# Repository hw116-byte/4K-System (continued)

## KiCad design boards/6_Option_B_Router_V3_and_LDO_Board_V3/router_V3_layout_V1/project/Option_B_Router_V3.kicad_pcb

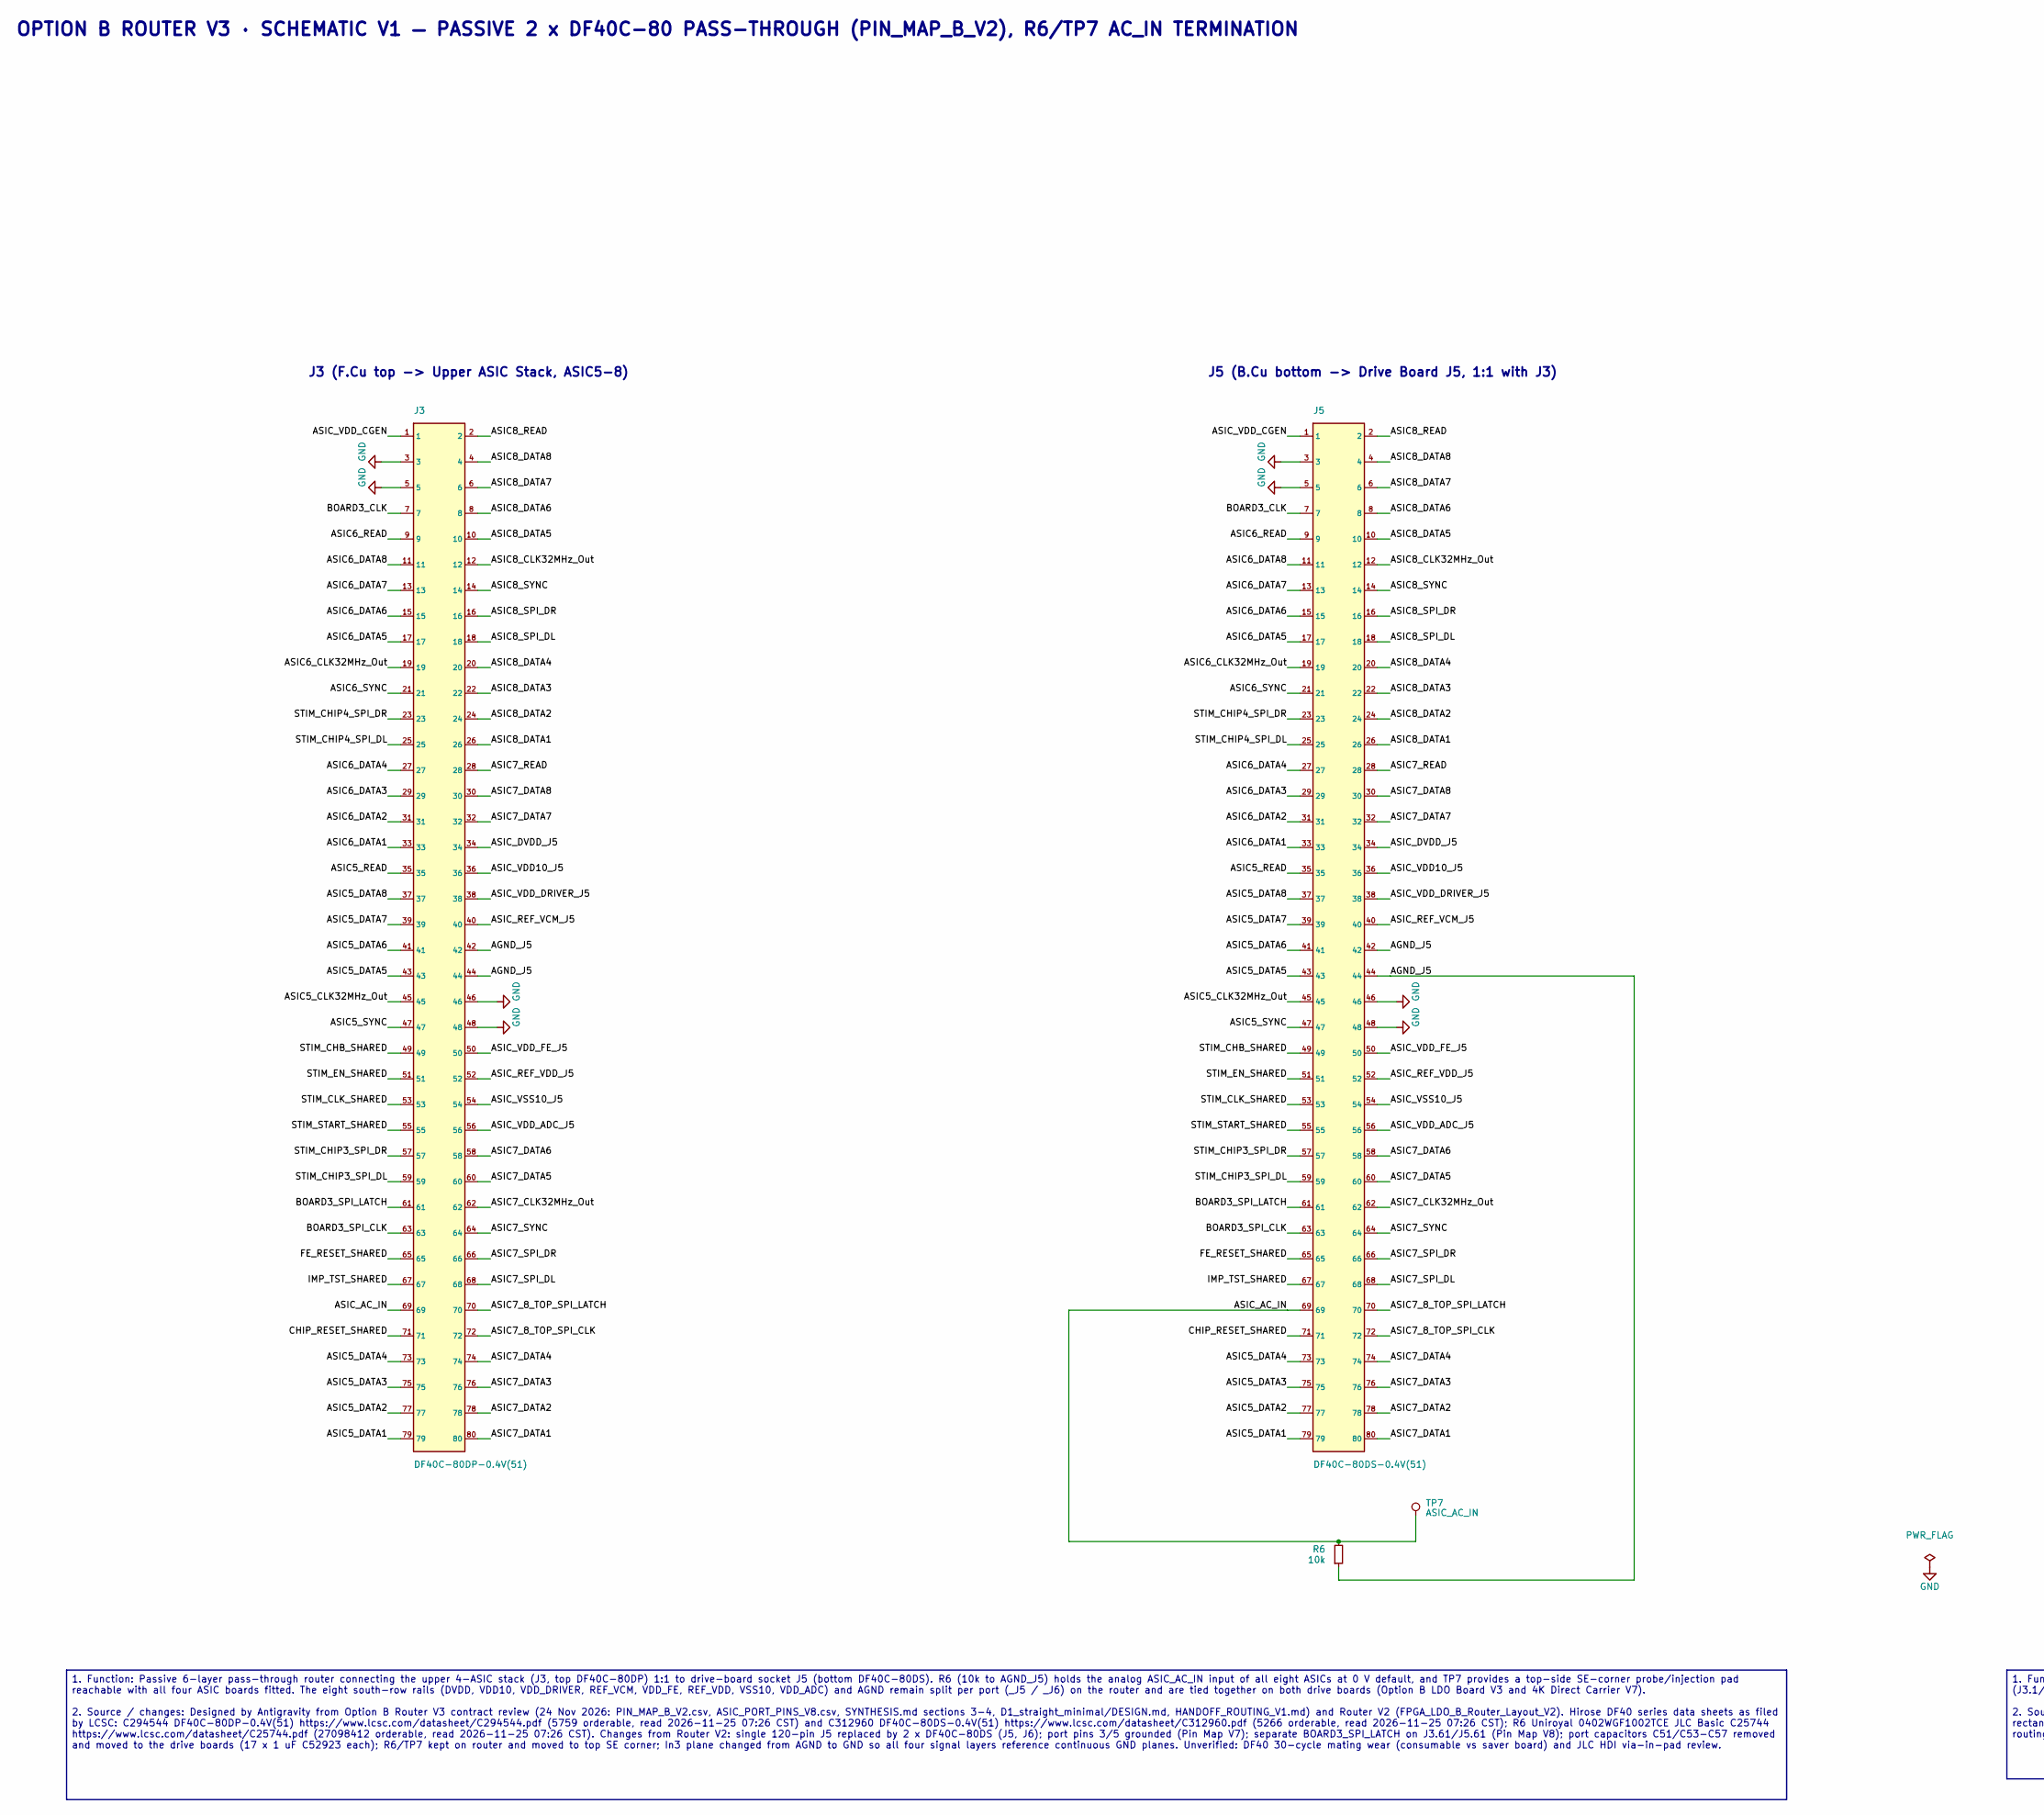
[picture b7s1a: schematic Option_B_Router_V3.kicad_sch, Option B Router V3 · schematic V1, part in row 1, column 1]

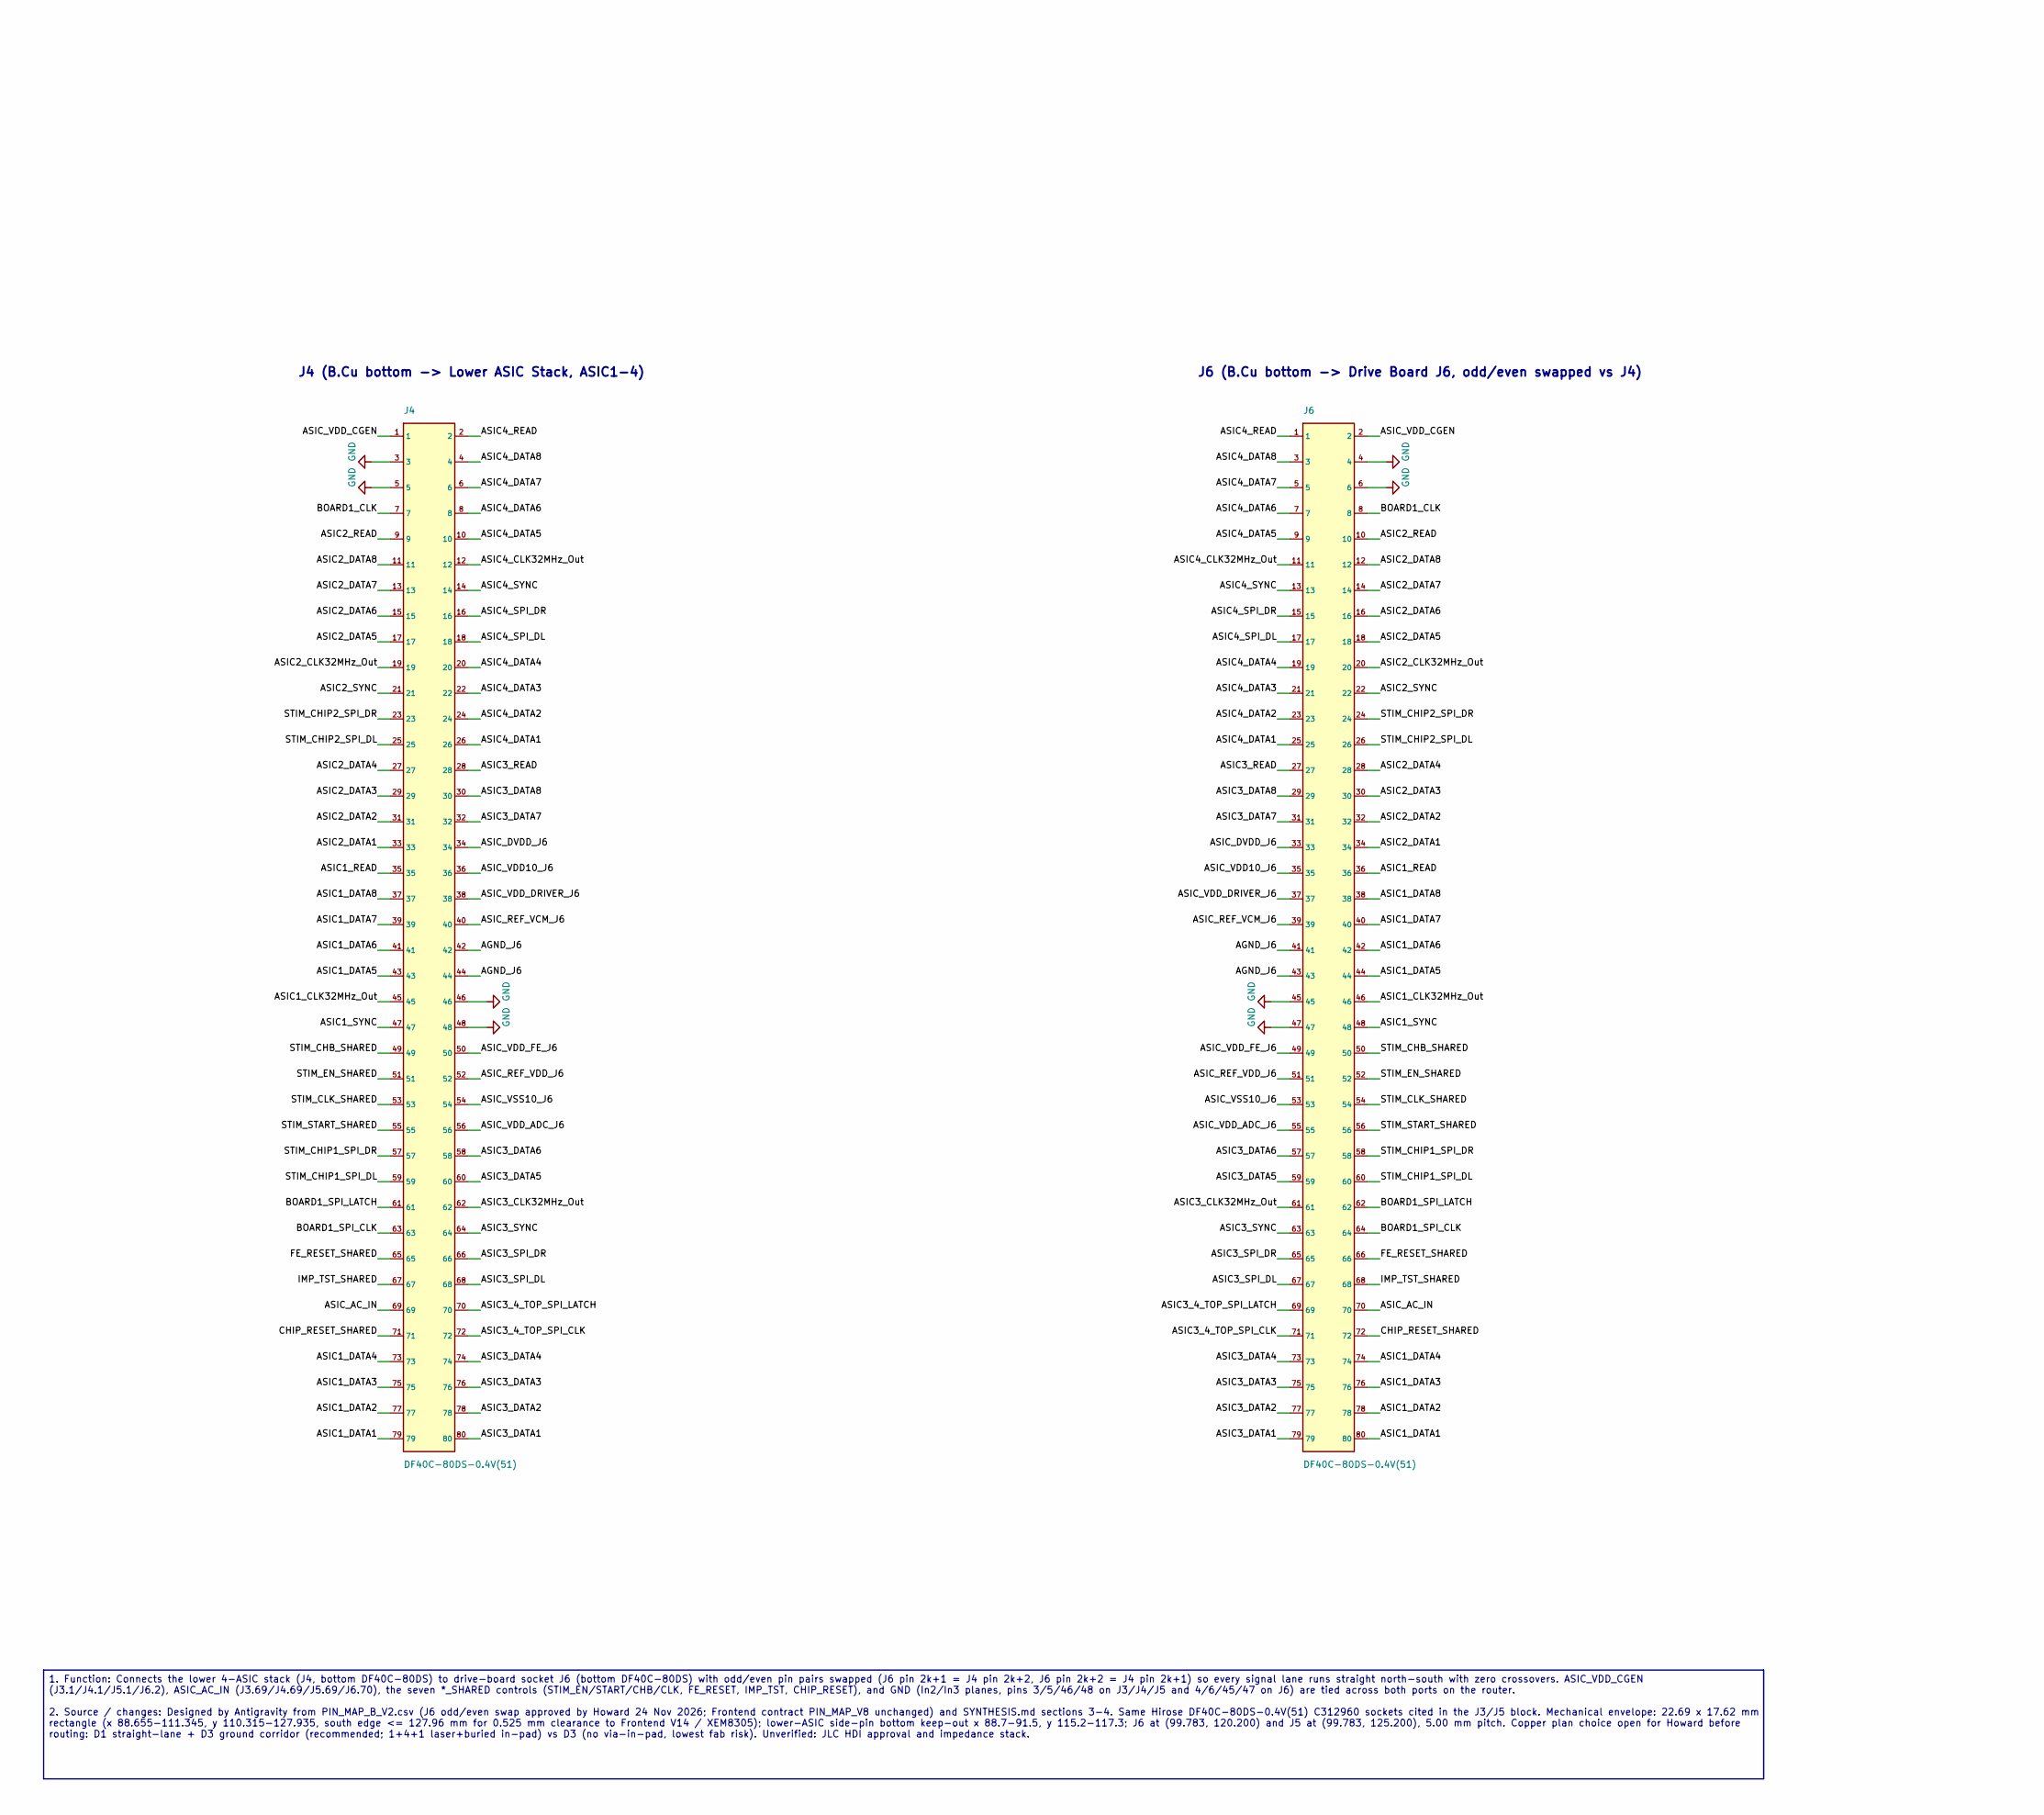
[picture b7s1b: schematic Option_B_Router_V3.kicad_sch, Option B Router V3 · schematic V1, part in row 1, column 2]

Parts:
J3: DF40C-80DP-0.4V(51); Hirose_DF40C-80DP-0.4V_2x40-1MP_P0.4mm; MPN DF40C-80DP-0.4V(51); LCSC C294544
J4, J5, J6: DF40C-80DS-0.4V(51); Hirose_DF40C-80DS-0.4V_2x40_P0.4mm; MPN DF40C-80DS-0.4V(51); LCSC C312960
R6: 10k; R_0402_1005Metric; MPN Uniroyal 0402WGF1002TCE (10k 1% 0402); LCSC C25744
TP7: ASIC_AC_IN; TestPoint_Pad_D1.0mm_Compact

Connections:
/AGND_J5: J3.42, J3.44, J5.42, J5.44, R6.2
/AGND_J6: J4.42, J4.44, J6.41, J6.43
/ASIC1_CLK32MHz_Out: J4.45, J6.46
/ASIC1_DATA1: J4.79, J6.80
/ASIC1_DATA2: J4.77, J6.78
/ASIC1_DATA3: J4.75, J6.76
/ASIC1_DATA4: J4.73, J6.74
/ASIC1_DATA5: J4.43, J6.44
/ASIC1_DATA6: J4.41, J6.42
/ASIC1_DATA7: J4.39, J6.40
/ASIC1_DATA8: J4.37, J6.38
/ASIC1_READ: J4.35, J6.36
/ASIC1_SYNC: J4.47, J6.48
/ASIC2_CLK32MHz_Out: J4.19, J6.20
/ASIC2_DATA1: J4.33, J6.34
/ASIC2_DATA2: J4.31, J6.32
/ASIC2_DATA3: J4.29, J6.30
/ASIC2_DATA4: J4.27, J6.28
/ASIC2_DATA5: J4.17, J6.18
/ASIC2_DATA6: J4.15, J6.16
/ASIC2_DATA7: J4.13, J6.14
/ASIC2_DATA8: J4.11, J6.12
/ASIC2_READ: J4.9, J6.10
/ASIC2_SYNC: J4.21, J6.22
/ASIC3_4_TOP_SPI_CLK: J4.72, J6.71
/ASIC3_4_TOP_SPI_LATCH: J4.70, J6.69
/ASIC3_CLK32MHz_Out: J4.62, J6.61
/ASIC3_DATA1: J4.80, J6.79
/ASIC3_DATA2: J4.78, J6.77
/ASIC3_DATA3: J4.76, J6.75
/ASIC3_DATA4: J4.74, J6.73
/ASIC3_DATA5: J4.60, J6.59
/ASIC3_DATA6: J4.58, J6.57
/ASIC3_DATA7: J4.32, J6.31
/ASIC3_DATA8: J4.30, J6.29
/ASIC3_READ: J4.28, J6.27
/ASIC3_SPI_DL: J4.68, J6.67
/ASIC3_SPI_DR: J4.66, J6.65
/ASIC3_SYNC: J4.64, J6.63
/ASIC4_CLK32MHz_Out: J4.12, J6.11
/ASIC4_DATA1: J4.26, J6.25
/ASIC4_DATA2: J4.24, J6.23
/ASIC4_DATA3: J4.22, J6.21
/ASIC4_DATA4: J4.20, J6.19
/ASIC4_DATA5: J4.10, J6.9
/ASIC4_DATA6: J4.8, J6.7
/ASIC4_DATA7: J4.6, J6.5
/ASIC4_DATA8: J4.4, J6.3
/ASIC4_READ: J4.2, J6.1
/ASIC4_SPI_DL: J4.18, J6.17
/ASIC4_SPI_DR: J4.16, J6.15
/ASIC4_SYNC: J4.14, J6.13
/ASIC5_CLK32MHz_Out: J3.45, J5.45
/ASIC5_DATA1: J3.79, J5.79
/ASIC5_DATA2: J3.77, J5.77
/ASIC5_DATA3: J3.75, J5.75
/ASIC5_DATA4: J3.73, J5.73
/ASIC5_DATA5: J3.43, J5.43
/ASIC5_DATA6: J3.41, J5.41
/ASIC5_DATA7: J3.39, J5.39
/ASIC5_DATA8: J3.37, J5.37
/ASIC5_READ: J3.35, J5.35
/ASIC5_SYNC: J3.47, J5.47
/ASIC6_CLK32MHz_Out: J3.19, J5.19
/ASIC6_DATA1: J3.33, J5.33
/ASIC6_DATA2: J3.31, J5.31
/ASIC6_DATA3: J3.29, J5.29
/ASIC6_DATA4: J3.27, J5.27
/ASIC6_DATA5: J3.17, J5.17
/ASIC6_DATA6: J3.15, J5.15
/ASIC6_DATA7: J3.13, J5.13
/ASIC6_DATA8: J3.11, J5.11
/ASIC6_READ: J3.9, J5.9
/ASIC6_SYNC: J3.21, J5.21
/ASIC7_8_TOP_SPI_CLK: J3.72, J5.72
/ASIC7_8_TOP_SPI_LATCH: J3.70, J5.70
/ASIC7_CLK32MHz_Out: J3.62, J5.62
/ASIC7_DATA1: J3.80, J5.80
/ASIC7_DATA2: J3.78, J5.78
/ASIC7_DATA3: J3.76, J5.76
/ASIC7_DATA4: J3.74, J5.74
/ASIC7_DATA5: J3.60, J5.60
/ASIC7_DATA6: J3.58, J5.58
/ASIC7_DATA7: J3.32, J5.32
/ASIC7_DATA8: J3.30, J5.30
/ASIC7_READ: J3.28, J5.28
/ASIC7_SPI_DL: J3.68, J5.68
/ASIC7_SPI_DR: J3.66, J5.66
/ASIC7_SYNC: J3.64, J5.64
/ASIC8_CLK32MHz_Out: J3.12, J5.12
/ASIC8_DATA1: J3.26, J5.26
/ASIC8_DATA2: J3.24, J5.24
/ASIC8_DATA3: J3.22, J5.22
/ASIC8_DATA4: J3.20, J5.20
/ASIC8_DATA5: J3.10, J5.10
/ASIC8_DATA6: J3.8, J5.8
/ASIC8_DATA7: J3.6, J5.6
/ASIC8_DATA8: J3.4, J5.4
/ASIC8_READ: J3.2, J5.2
/ASIC8_SPI_DL: J3.18, J5.18
/ASIC8_SPI_DR: J3.16, J5.16
/ASIC8_SYNC: J3.14, J5.14
/ASIC_AC_IN: J3.69, J4.69, J5.69, J6.70, R6.1, TP7.1
/ASIC_DVDD_J5: J3.34, J5.34
/ASIC_DVDD_J6: J4.34, J6.33
/ASIC_REF_VCM_J5: J3.40, J5.40
/ASIC_REF_VCM_J6: J4.40, J6.39
/ASIC_REF_VDD_J5: J3.52, J5.52
/ASIC_REF_VDD_J6: J4.52, J6.51
/ASIC_VDD10_J5: J3.36, J5.36
/ASIC_VDD10_J6: J4.36, J6.35
/ASIC_VDD_ADC_J5: J3.56, J5.56
/ASIC_VDD_ADC_J6: J4.56, J6.55
/ASIC_VDD_CGEN: J3.1, J4.1, J5.1, J6.2
/ASIC_VDD_DRIVER_J5: J3.38, J5.38
/ASIC_VDD_DRIVER_J6: J4.38, J6.37
/ASIC_VDD_FE_J5: J3.50, J5.50
/ASIC_VDD_FE_J6: J4.50, J6.49
/ASIC_VSS10_J5: J3.54, J5.54
/ASIC_VSS10_J6: J4.54, J6.53
/BOARD1_CLK: J4.7, J6.8
/BOARD1_SPI_CLK: J4.63, J6.64
/BOARD1_SPI_LATCH: J4.61, J6.62
/BOARD3_CLK: J3.7, J5.7
/BOARD3_SPI_CLK: J3.63, J5.63
/BOARD3_SPI_LATCH: J3.61, J5.61
/CHIP_RESET_SHARED: J3.71, J4.71, J5.71, J6.72
/FE_RESET_SHARED: J3.65, J4.65, J5.65, J6.66
/IMP_TST_SHARED: J3.67, J4.67, J5.67, J6.68
/STIM_CHB_SHARED: J3.49, J4.49, J5.49, J6.50
/STIM_CHIP1_SPI_DL: J4.59, J6.60
/STIM_CHIP1_SPI_DR: J4.57, J6.58
/STIM_CHIP2_SPI_DL: J4.25, J6.26
/STIM_CHIP2_SPI_DR: J4.23, J6.24
/STIM_CHIP3_SPI_DL: J3.59, J5.59
/STIM_CHIP3_SPI_DR: J3.57, J5.57
/STIM_CHIP4_SPI_DL: J3.25, J5.25
/STIM_CHIP4_SPI_DR: J3.23, J5.23
/STIM_CLK_SHARED: J3.53, J4.53, J5.53, J6.54
/STIM_EN_SHARED: J3.51, J4.51, J5.51, J6.52
/STIM_START_SHARED: J3.55, J4.55, J5.55, J6.56
GND: J3.3, J3.5, J3.46, J3.48, J4.3, J4.5, J4.46, J4.48, J5.3, J5.5, J5.46, J5.48, J6.4, J6.6, J6.45, J6.47

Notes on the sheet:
J3 (F.Cu top -> Upper ASIC Stack, ASIC5-8)
J5 (B.Cu bottom -> Drive Board J5, 1:1 with J3)
J4 (B.Cu bottom -> Lower ASIC Stack, ASIC1-4)
J6 (B.Cu bottom -> Drive Board J6, odd/even swapped vs J4)
1. Function: Passive 6-layer pass-through router connecting the upper 4-ASIC stack (J3, top DF40C-80DP) 1:1 to drive-board socket J5 (bottom DF40C-80DS). R6 (10k to AGND_J5) holds the analog ASIC_AC_IN input of all eight ASICs at 0 V default, and TP7 provides a top-side SE-corner probe/injection pa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
1. Function: Connects the lower 4-ASIC stack (J4, bottom DF40C-80DS) to drive-board socket J6 (bottom DF40C-80DS) with odd/even pin pairs swapped (J6 pin 2k+1 = J4 pin 2k+2, J6 pin 2k+2 = J4 pin 2k+1) so every signal lane runs straight north-south with zero crossovers. ASIC_VDD_CGEN (J3.1/J4.1/J5.1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
OPTION B ROUTER V3 · SCHEMATIC V1 — PASSIVE 2 x DF40C-80 PASS-THROUGH (PIN_MAP_B_V2), R6/TP7 AC_IN TERMINATION

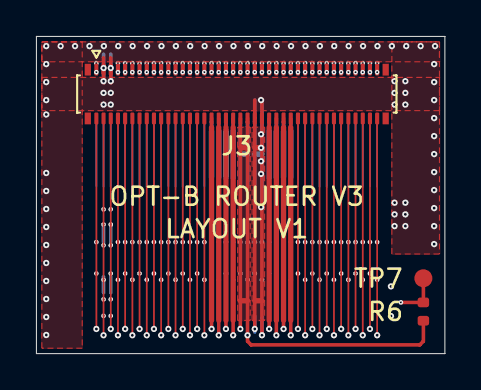
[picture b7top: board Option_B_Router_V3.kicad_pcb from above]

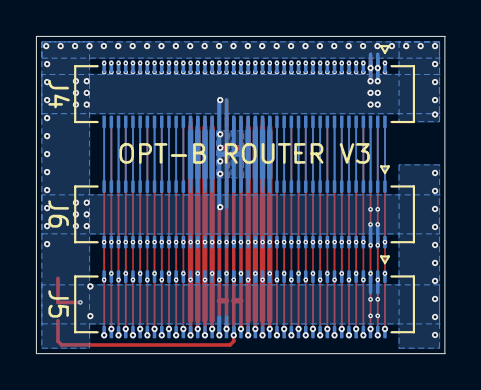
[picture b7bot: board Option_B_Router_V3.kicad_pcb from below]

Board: 6 copper layers, 22.7 x 17.6 mm, 6 parts (3 on the bottom side), 142 nets.

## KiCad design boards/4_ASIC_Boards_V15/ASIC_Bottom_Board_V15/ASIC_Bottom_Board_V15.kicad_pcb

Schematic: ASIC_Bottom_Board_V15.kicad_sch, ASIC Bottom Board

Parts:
C1, C2, C4, C5, C6, C7, C14, C18, C25, C33, C34, C41, C42, C46, C48: 10nF; C_0201_0603Metric; MPN GRM033R71E103KE14D; LCSC C85930
C19, C26, C50, C51, C52, C53, C54, C55, C56, C57, C58, C59, C60, C61, C62, C63: 100nF; C_0201_0603Metric; MPN CL03A104KA3NNNC; LCSC C307379
J1: Conn_01x01_Pin; PinHeader_1x01_P1.00mm_Horizontal; not fitted
J3: DF40C-80DS-0.4V(51); Hirose_DF40C-80DS-0.4V_2x40_P0.4mm; MPN DF40C-80DS-0.4V(51); LCSC C312960
J4: DF40C-80DP-0.4V(51); Hirose_DF40C-80DP-0.4V_2x40-1MP_P0.4mm; MPN DF40C-80DP-0.4V(51); LCSC C294544
U01_BCD1, U01_BCD2: *; U01_BCD_OFF_CHIP; not fitted

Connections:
/AC_IN: J3.69, J4.69, U01_BCD1.AC_IN, U01_BCD2.AC_IN
/AGND: C1.2, C2.2, C4.2, C5.2, C6.2, C18.2, C19.2, C25.2, C26.2, C33.2, C34.2, C41.2, C42.2, C46.2, C48.2, C50.2, C51.2, C52.2, C53.2, C54.2, C55.2, C56.2, C57.2, C58.2, C59.2, C60.2, C63.2, J1.1 (Pin_1_1), J3.42, J3.44, J4.42, J4.44, U01_BCD1.AGND2, U01_BCD1.AGND_1, U01_BCD1.LAGND_1, U01_BCD1.LAGND_2, U01_BCD1.LAGND_3, U01_BCD1.LAGND_4, U01_BCD1.LAGND_5, U01_BCD1.LAGND_6, U01_BCD1.LAGND_7, U01_BCD1.LAGND_8, U01_BCD1.LAGND_9, U01_BCD1.LAGND_10, U01_BCD1.LAGND_11, U01_BCD1.LAGND_12, U01_BCD1.LAGND_13, U01_BCD1.LAGND_14, U01_BCD1.LAGND_15, U01_BCD1.LREF_GND1, U01_BCD1.LREF_GND2, U01_BCD1.LREF_GND3, U01_BCD1.LREF_GND4, U01_BCD1.RAGND_1, U01_BCD1.RAGND_2, U01_BCD1.RAGND_3, U01_BCD1.RAGND_4, U01_BCD1.RAGND_5, U01_BCD1.RAGND_6, U01_BCD1.RAGND_7, U01_BCD1.RAGND_8, U01_BCD1.RAGND_9, U01_BCD1.RAGND_10, U01_BCD1.RAGND_11, U01_BCD1.RAGND_12, U01_BCD1.RAGND_13, U01_BCD1.RAGND_14, U01_BCD1.RAGND_15, U01_BCD1.REF_1, U01_BCD1.REF_2, U01_BCD1.REF_3, U01_BCD1.REF_4, U01_BCD1.RREF_GND1, U01_BCD1.RREF_GND2, U01_BCD1.RREF_GND3, U01_BCD1.RREF_GND4, U01_BCD2.AGND2, U01_BCD2.AGND_1, U01_BCD2.LAGND_1, U01_BCD2.LAGND_2, U01_BCD2.LAGND_3, U01_BCD2.LAGND_4, U01_BCD2.LAGND_5, U01_BCD2.LAGND_6, U01_BCD2.LAGND_7, U01_BCD2.LAGND_8, U01_BCD2.LAGND_9, U01_BCD2.LAGND_10, U01_BCD2.LAGND_11, U01_BCD2.LAGND_12, U01_BCD2.LAGND_13, U01_BCD2.LAGND_14, U01_BCD2.LAGND_15, U01_BCD2.LREF_GND1, U01_BCD2.LREF_GND2, U01_BCD2.LREF_GND3, U01_BCD2.LREF_GND4, U01_BCD2.RAGND_1, U01_BCD2.RAGND_2, U01_BCD2.RAGND_3, U01_BCD2.RAGND_4, U01_BCD2.RAGND_5, U01_BCD2.RAGND_6, U01_BCD2.RAGND_7, U01_BCD2.RAGND_8, U01_BCD2.RAGND_9, U01_BCD2.RAGND_10, U01_BCD2.RAGND_11, U01_BCD2.RAGND_12, U01_BCD2.RAGND_13, U01_BCD2.RAGND_14, U01_BCD2.RAGND_15, U01_BCD2.REF_1, U01_BCD2.REF_2, U01_BCD2.REF_3, U01_BCD2.REF_4, U01_BCD2.RREF_GND1, U01_BCD2.RREF_GND2, U01_BCD2.RREF_GND3, U01_BCD2.RREF_GND4
/CHIP_RESET: J3.71, J4.71, U01_BCD1.RRST_DIGITAL, U01_BCD1.RST_DRIVER, U01_BCD2.RRST_DIGITAL, U01_BCD2.RST_DRIVER
/CLK32MHZ: J3.45, J4.45, U01_BCD1.CLK32MHZ
/CLK32MHZ(2): J3.19, J4.19, U01_BCD2.CLK32MHZ
/CLKH: J3.7, J4.7, U01_BCD1.CLKH, U01_BCD2.CLKH
/D<1>: J3.79, J4.79, U01_BCD1.DATAL<4>
/D<1>(2): J3.33, J4.33, U01_BCD2.DATAL<4>
/D<2>: J3.77, J4.77, U01_BCD1.DATAL<3>
/D<2>(2): J3.31, J4.31, U01_BCD2.DATAL<3>
/D<3>: J3.75, J4.75, U01_BCD1.DATAL<2>
/D<3>(2): J3.29, J4.29, U01_BCD2.DATAL<2>
/D<4>: J3.73, J4.73, U01_BCD1.DATAL<1>
/D<4>(2): J3.27, J4.27, U01_BCD2.DATAL<1>
/D<5>: J3.43, J4.43, U01_BCD1.DATAR<4>
/D<5>(2): J3.17, J4.17, U01_BCD2.DATAR<4>
/D<6>: J3.41, J4.41, U01_BCD1.DATAR<3>
/D<6>(2): J3.15, J4.15, U01_BCD2.DATAR<3>
/D<7>: J3.39, J4.39, U01_BCD1.DATAR<2>
/D<7>(2): J3.13, J4.13, U01_BCD2.DATAR<2>
/D<8>: J3.37, J4.37, U01_BCD1.DATAR<1>
/D<8>(2): J3.11, J4.11, U01_BCD2.DATAR<1>
/DGND: C7.2, C14.2, C61.2, C62.2, J3.3, J3.5, J3.46, J3.48, J4.3, J4.5, J4.46, J4.48, U01_BCD1.DGND1, U01_BCD1.DGND2, U01_BCD1.DGND3, U01_BCD1.DGND4, U01_BCD1.EN_LDO, U01_BCD1.LDGND_1, U01_BCD1.LDGND_2, U01_BCD1.LDGND_3, U01_BCD1.LDGND_4, U01_BCD1.LDGND_5, U01_BCD1.LDGND_6, U01_BCD1.LDGND_7, U01_BCD1.LDGND_8, U01_BCD1.LDGND_9, U01_BCD1.LDGND_10, U01_BCD1.LDGND_11, U01_BCD1.LDGND_12, U01_BCD1.LDGND_13, U01_BCD1.RDGND_1, U01_BCD1.RDGND_2, U01_BCD1.RDGND_3, U01_BCD1.RDGND_4, U01_BCD1.RDGND_5, U01_BCD1.RDGND_6, U01_BCD1.RDGND_7, U01_BCD1.RDGND_8, U01_BCD1.RDGND_9, U01_BCD1.RDGND_10, U01_BCD1.RDGND_11, U01_BCD1.RDGND_12, U01_BCD1.RDGND_13, U01_BCD2.DGND1, U01_BCD2.DGND2, U01_BCD2.DGND3, U01_BCD2.DGND4, U01_BCD2.EN_LDO, U01_BCD2.LDGND_1, U01_BCD2.LDGND_2, U01_BCD2.LDGND_3, U01_BCD2.LDGND_4, U01_BCD2.LDGND_5, U01_BCD2.LDGND_6, U01_BCD2.LDGND_7, U01_BCD2.LDGND_8, U01_BCD2.LDGND_9, U01_BCD2.LDGND_10, U01_BCD2.LDGND_11, U01_BCD2.LDGND_12, U01_BCD2.LDGND_13, U01_BCD2.RDGND_1, U01_BCD2.RDGND_2, U01_BCD2.RDGND_3, U01_BCD2.RDGND_4, U01_BCD2.RDGND_5, U01_BCD2.RDGND_6, U01_BCD2.RDGND_7, U01_BCD2.RDGND_8, U01_BCD2.RDGND_9, U01_BCD2.RDGND_10, U01_BCD2.RDGND_11, U01_BCD2.RDGND_12, U01_BCD2.RDGND_13
/DVDD: C7.1, C14.1, C61.1, C62.1, J3.34, J4.34, U01_BCD1.CGEN_RST, U01_BCD1.LDVDD_B1, U01_BCD1.LDVDD_B2, U01_BCD1.LDVDD_B3, U01_BCD1.LDVDD_T1, U01_BCD1.LDVDD_T2, U01_BCD1.LDVDD_T3, U01_BCD1.RDVDD_B1, U01_BCD1.RDVDD_B2, U01_BCD1.RDVDD_B3, U01_BCD1.RDVDD_T1, U01_BCD1.RDVDD_T2, U01_BCD1.RDVDD_T3, U01_BCD1.SPI_LDO_O, U01_BCD1.SPI_LDO_P, U01_BCD1.SPI_LDO_P1, U01_BCD1.SPI_LDO_P2, U01_BCD2.CGEN_RST, U01_BCD2.LDVDD_B1, U01_BCD2.LDVDD_B2, U01_BCD2.LDVDD_B3, U01_BCD2.LDVDD_T1, U01_BCD2.LDVDD_T2, U01_BCD2.LDVDD_T3, U01_BCD2.RDVDD_B1, U01_BCD2.RDVDD_B2, U01_BCD2.RDVDD_B3, U01_BCD2.RDVDD_T1, U01_BCD2.RDVDD_T2, U01_BCD2.RDVDD_T3, U01_BCD2.SPI_LDO_O, U01_BCD2.SPI_LDO_P, U01_BCD2.SPI_LDO_P1, U01_BCD2.SPI_LDO_P2
/FE_RESET: J3.65, J4.65, U01_BCD1.RST_FEL, U01_BCD1.RST_FER, U01_BCD2.RST_FEL, U01_BCD2.RST_FER
/IMP_TEST: J3.67, J4.67, U01_BCD1.IMP_TST, U01_BCD2.IMP_TST
/READ: J3.35, J4.35, U01_BCD1.READ
/READ(2): J3.9, J4.9, U01_BCD2.READ
/REF_VCM: C5.1, C46.1, C57.1, C58.1, J3.40, J4.40, U01_BCD1.LREF_VCM1, U01_BCD1.LREF_VCM2, U01_BCD1.LREF_VCM3, U01_BCD1.LREF_VCM4, U01_BCD1.RREF_VCM1, U01_BCD1.RREF_VCM2, U01_BCD1.RREF_VCM3, U01_BCD1.RREF_VCM4, U01_BCD1.VCM, U01_BCD2.LREF_VCM1, U01_BCD2.LREF_VCM2, U01_BCD2.LREF_VCM3, U01_BCD2.LREF_VCM4, U01_BCD2.RREF_VCM1, U01_BCD2.RREF_VCM2, U01_BCD2.RREF_VCM3, U01_BCD2.RREF_VCM4, U01_BCD2.VCM
/REF_VDD: C2.1, C33.1, C55.1, C56.1, J3.52, J4.52, U01_BCD1.LREF_VDD1, U01_BCD1.LREF_VDD2, U01_BCD1.LREF_VDD3, U01_BCD1.LREF_VDD4, U01_BCD1.RREF_VDD1, U01_BCD1.RREF_VDD2, U01_BCD1.RREF_VDD3, U01_BCD1.RREF_VDD4, U01_BCD2.LREF_VDD1, U01_BCD2.LREF_VDD2, U01_BCD2.LREF_VDD3, U01_BCD2.LREF_VDD4, U01_BCD2.RREF_VDD1, U01_BCD2.RREF_VDD2, U01_BCD2.RREF_VDD3, U01_BCD2.RREF_VDD4
/SPI_CLK: J3.63, J4.63, U01_BCD1.SPI_CLK, U01_BCD2.SPI_CLK
/SPI_DINL: J3.59, J4.59, U01_BCD1.SPI_DINL
/SPI_DINL(2): J3.25, J4.25, U01_BCD2.SPI_DINL
/SPI_DINR: J3.57, J4.57, U01_BCD1.SPI_DINR
/SPI_DINR(2): J3.23, J4.23, U01_BCD2.SPI_DINR
/SPI_LATCH: J3.61, J4.61, U01_BCD1.SPI_LATCH, U01_BCD2.SPI_LATCH
/STIM_CHB: J3.49, J4.49, U01_BCD1.FPGA_CHBL, U01_BCD1.FPGA_CHBR, U01_BCD2.FPGA_CHBL, U01_BCD2.FPGA_CHBR
/STIM_CLK: J3.53, J4.53, U01_BCD1.FPGA_CLK, U01_BCD2.FPGA_CLK
/STIM_EN: J3.51, J4.51, U01_BCD1.FPGA_EN, U01_BCD2.FPGA_EN
/STIM_START: J3.55, J4.55, U01_BCD1.FPGA_START, U01_BCD2.FPGA_START
/SYNC: J3.47, J4.47, U01_BCD1.SYNC
/SYNC(2): J3.21, J4.21, U01_BCD2.SYNC
/T_CLK32MHZ: J3.62, J4.62
/T_CLK32MHZ(2): J3.12, J4.12
/T_D<1>: J3.80, J4.80
/T_D<1>(2): J3.26, J4.26
/T_D<2>: J3.78, J4.78
/T_D<2>(2): J3.24, J4.24
/T_D<3>: J3.76, J4.76
/T_D<3>(2): J3.22, J4.22
/T_D<4>: J3.74, J4.74
/T_D<4>(2): J3.20, J4.20
/T_D<5>: J3.60, J4.60
/T_D<5>(2): J3.10, J4.10
/T_D<6>: J3.58, J4.58
/T_D<6>(2): J3.8, J4.8
/T_D<7>: J3.32, J4.32
/T_D<7>(2): J3.6, J4.6
/T_D<8>: J3.30, J4.30
/T_D<8>(2): J3.4, J4.4
/T_READ: J3.28, J4.28
/T_READ(2): J3.2, J4.2
/T_SPI_CLK: J3.72, J4.72
/T_SPI_DINL: J3.68, J4.68
/T_SPI_DINL(2): J3.18, J4.18
/T_SPI_DINR: J3.66, J4.66
/T_SPI_DINR(2): J3.16, J4.16
/T_SPI_LATCH: J3.70, J4.70
/T_SYNC: J3.64, J4.64
/T_SYNC(2): J3.14, J4.14
/VDD10: C18.1, C19.1, J3.36, J4.36, U01_BCD1.P10_L, U01_BCD1.P10_R, U01_BCD2.P10_L, U01_BCD2.P10_R
/VDD_ADC: C1.1, C34.1, C53.1, C54.1, J3.56, J4.56, U01_BCD1.LVDD_ADC1, U01_BCD1.LVDD_ADC2, U01_BCD1.LVDD_ADC3, U01_BCD1.LVDD_ADC4, U01_BCD1.LVDD_ADC5, U01_BCD1.RVDD_ADC1, U01_BCD1.RVDD_ADC2, U01_BCD1.RVDD_ADC3, U01_BCD1.RVDD_ADC4, U01_BCD1.RVDD_ADC5, U01_BCD2.LVDD_ADC1, U01_BCD2.LVDD_ADC2, U01_BCD2.LVDD_ADC3, U01_BCD2.LVDD_ADC4, U01_BCD2.LVDD_ADC5, U01_BCD2.RVDD_ADC1, U01_BCD2.RVDD_ADC2, U01_BCD2.RVDD_ADC3, U01_BCD2.RVDD_ADC4, U01_BCD2.RVDD_ADC5
/VDD_CGEN: C6.1, C50.1, C63.1, J3.1, J4.1, U01_BCD1.VDD_CGEN, U01_BCD2.VDD_CGEN
/VDD_DRIVER: C41.1, C42.1, C59.1, C60.1, J3.38, J4.38, U01_BCD1.LVDD_DRIVER1, U01_BCD1.LVDD_DRIVER2, U01_BCD1.LVDD_DRIVER3, U01_BCD1.LVDD_DRIVER4, U01_BCD1.LVDD_DRIVER5, U01_BCD1.RVDD_DRIVER1, U01_BCD1.RVDD_DRIVER2, U01_BCD1.RVDD_DRIVER3, U01_BCD1.RVDD_DRIVER4, U01_BCD1.RVDD_DRIVER5, U01_BCD2.LVDD_DRIVER1, U01_BCD2.LVDD_DRIVER2, U01_BCD2.LVDD_DRIVER3, U01_BCD2.LVDD_DRIVER4, U01_BCD2.LVDD_DRIVER5, U01_BCD2.RVDD_DRIVER1, U01_BCD2.RVDD_DRIVER2, U01_BCD2.RVDD_DRIVER3, U01_BCD2.RVDD_DRIVER4, U01_BCD2.RVDD_DRIVER5
/VDD_FE: C4.1, C48.1, C51.1, C52.1, J3.50, J4.50, U01_BCD1.LVDD_FE1, U01_BCD1.LVDD_FE2, U01_BCD1.LVDD_FE3, U01_BCD1.LVDD_FE4, U01_BCD1.RVDD_FE1, U01_BCD1.RVDD_FE2, U01_BCD1.RVDD_FE3, U01_BCD1.RVDD_FE4, U01_BCD2.LVDD_FE1, U01_BCD2.LVDD_FE2, U01_BCD2.LVDD_FE3, U01_BCD2.LVDD_FE4, U01_BCD2.RVDD_FE1, U01_BCD2.RVDD_FE2, U01_BCD2.RVDD_FE3, U01_BCD2.RVDD_FE4
/VSS10: C25.1, C26.1, J3.54, J4.54, U01_BCD1.M10_L, U01_BCD1.M10_R, U01_BCD2.M10_L, U01_BCD2.M10_R

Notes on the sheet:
Function: The DISC_OUT finger of U01_BCD1 is left open (no-connect flag). Nothing on this board reads or drives it. Source / changes: Inherited from the ASIC designer's board pair; not a datasheet circuit. Changed in V6 by Claude: the wire stub and the label DISC_OUT at this finger are removed, so 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
Function: The DISC_OUT finger of U01_BCD2 is left open (no-connect flag). Nothing on this board reads or drives it. Source / changes: Inherited from the ASIC designer's board pair; not a datasheet circuit. Changed in V6 by Claude: the wire stub and the label DISC_OUT(2) at this finger are removed, 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
Function: J1 is a single AGND pin. It is not fitted: marked do-not-populate, left out of the BOM and left out of the position file. Its hole and AGND connection stay on the board. Source / changes: Inherited from the ASIC designer's board; not a datasheet circuit. Changed in V6 by Claude: the DNP a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
Function: local decoupling for the ASIC supply rails. Each 1.5 V rail has two capacitors per chip on B.Cu under the dies (10 nF nearest the die, 100 nF in the outer row). VDD_CGEN, VDD10 (+8 V) and VSS10 (-8 V) have their pairs on F.Cu at the connector, and C63 adds a VDD_CGEN capacitor beside chip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
Function: J3 (receptacle, underside) and J4 (plug, top side) are the 80-contact stacking connectors of the head. Each J3 contact goes to the same-numbered J4 contact, so all 80 lines pass through this board to the next one. Pins 3 and 5 are DGND (pin map V7). Source / changes: pin order inherited f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

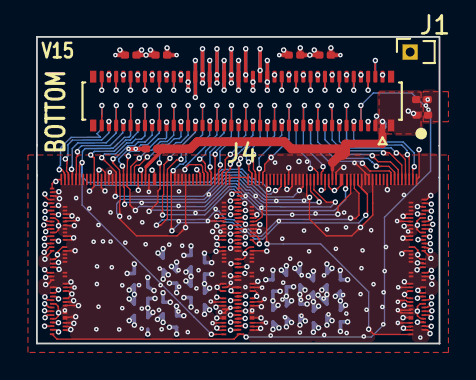
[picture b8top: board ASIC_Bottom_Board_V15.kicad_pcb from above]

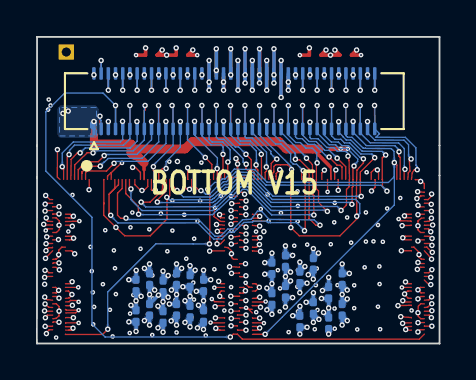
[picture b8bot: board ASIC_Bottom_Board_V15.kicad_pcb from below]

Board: 10 copper layers, 22.4 x 17.0 mm, 36 parts (25 on the bottom side), 76 nets.
